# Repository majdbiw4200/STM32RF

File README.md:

# STM32RF
RF to USB design using STM32 microcontroller. The design is a remake of Philip Salmony design https://github.com/pms67/STRF-Kicad

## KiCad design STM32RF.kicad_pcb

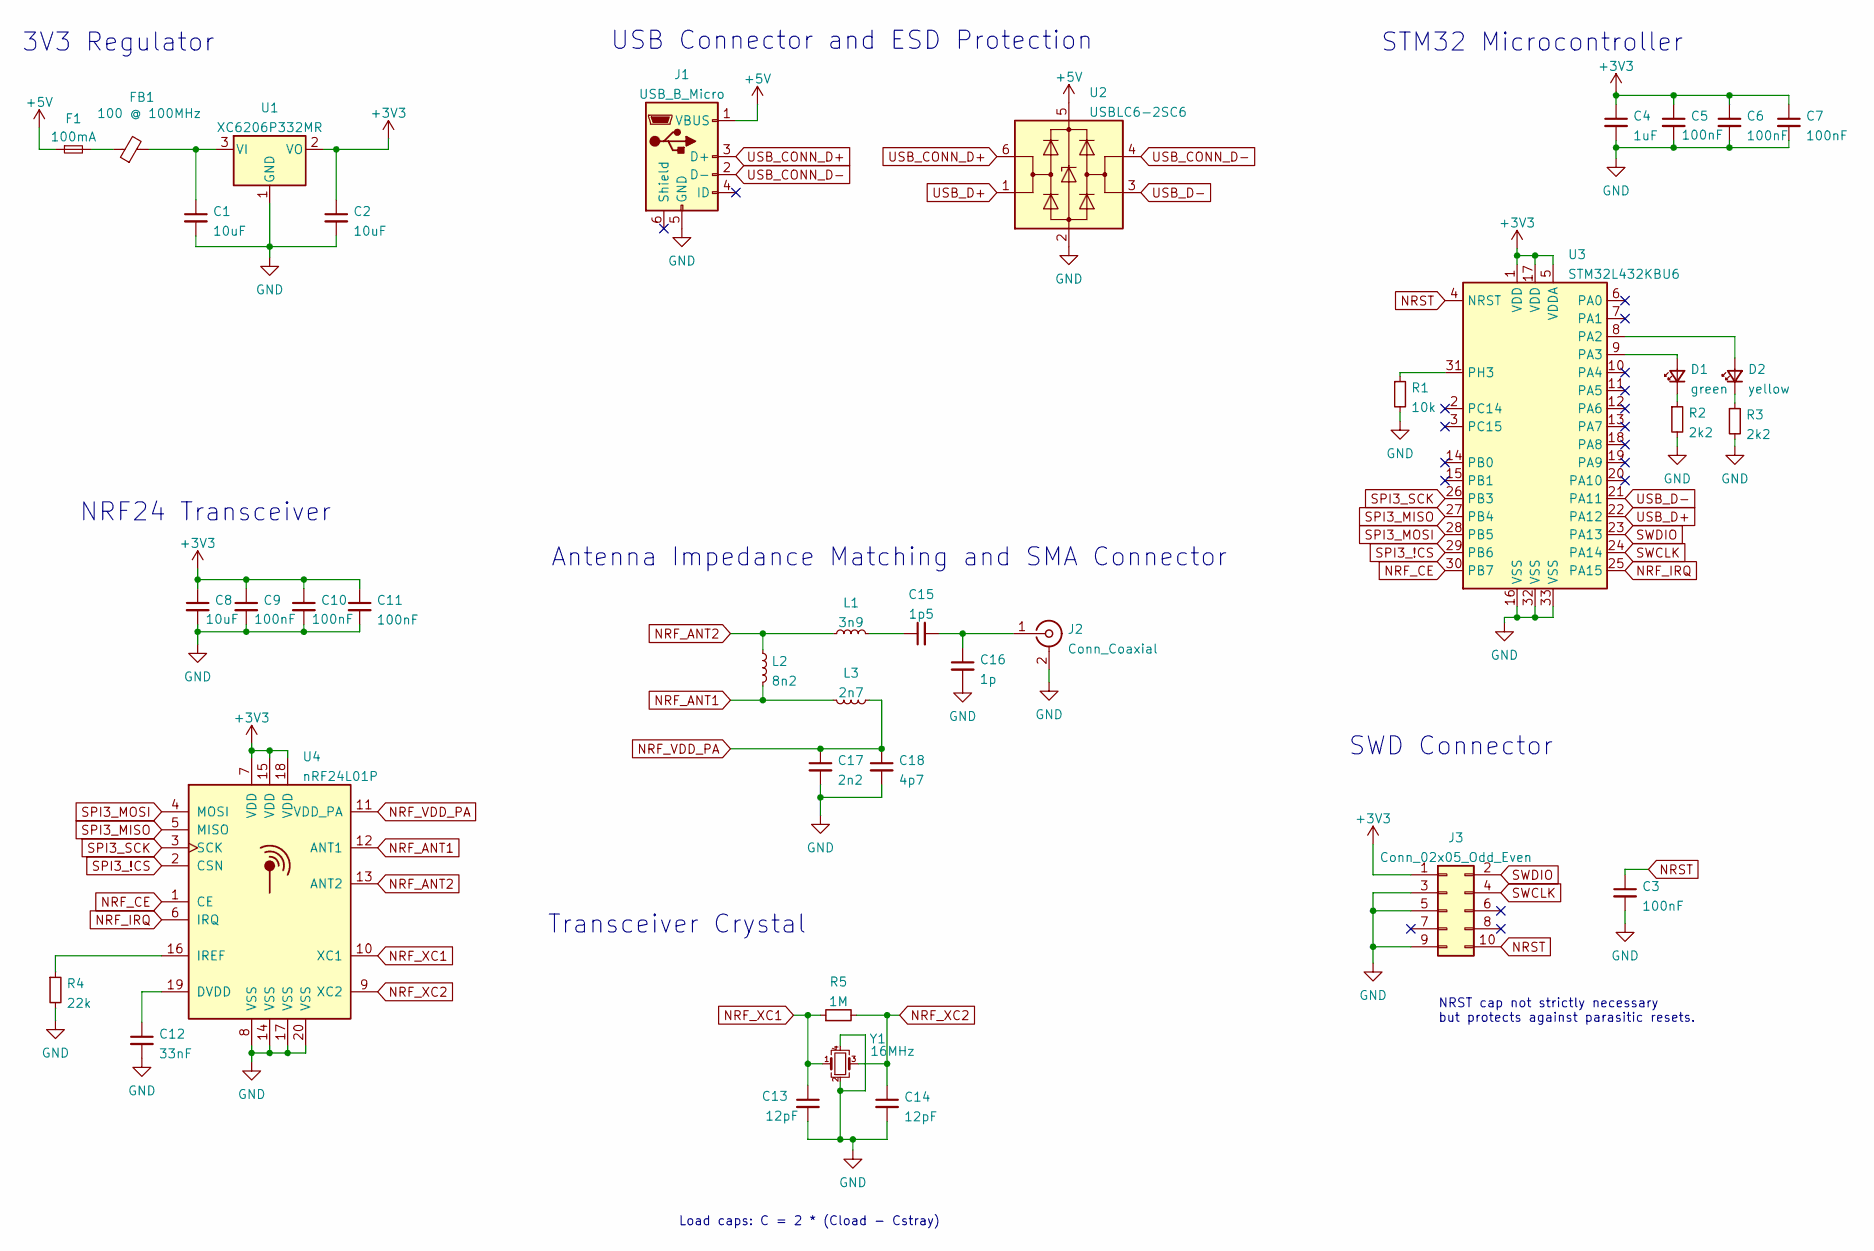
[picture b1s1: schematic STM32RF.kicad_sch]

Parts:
C1, C2, C8: 10uF; C_0603_1608Metric; LCSC Part # C19702
C3, C5, C6, C7, C9, C10, C11: 100nF; C_0402_1005Metric; LCSC Part # C1525
C4: 1uF; C_0402_1005Metric; LCSC Part # C14445
C12: 33nF; C_0402_1005Metric; LCSC Part # C472437
C13, C14: 12pF; C_0402_1005Metric; LCSC Part # C472446
C15: 1p5; C_0402_1005Metric; LCSC Part # C170150
C16: 1p; C_0402_1005Metric; LCSC Part # C307340
C17: 2n2; C_0402_1005Metric; LCSC Part # C84703
C18: 4p7; C_0402_1005Metric; LCSC Part # C318595
D1: green; LED_0603_1608Metric; LCSC Part # C72043
D2: yellow; LED_0603_1608Metric; LCSC Part # C72038
F1: 100mA; Fuse_1206_3216Metric
FB1: 100 @ 100MHz; L_0805_2012Metric; LCSC Part # C1015
J1: USB_B_Micro; USB_Micro-B_Molex_47346-0001
J2: Conn_Coaxial; SMA_Samtec_SMA-J-P-X-ST-EM1_EdgeMount
J3: Conn_02x05_Odd_Even; PinHeader_2x05_P1.27mm_Vertical
L1: 3n9; L_0402_1005Metric; LCSC Part # C14033
L2: 8n2; L_0402_1005Metric; LCSC Part # C16208
L3: 2n7; L_0402_1005Metric; LCSC Part # C27123
R1: 10k; R_0402_1005Metric; LCSC Part # C25744
R2, R3: 2k2; R_0603_1608Metric; LCSC Part # C4190
R4: 22k; R_0402_1005Metric; LCSC Part # C25768
R5: 1M; R_0402_1005Metric; LCSC Part # C26083
U1: XC6206P332MR; SOT-23; LCSC Part # C5446
U2: USBLC6-2SC6; SOT-23-6; LCSC Part # C7519
U3: STM32L432KBU6; QFN-32-1EP_5x5mm_P0.5mm_EP3.45x3.45mm; LCSC Part # C94784
U4: nRF24L01P; QFN-20-1EP_4x4mm_P0.5mm_EP2.5x2.5mm; LCSC Part # C8791
Y1: 16MHz; Crystal_SMD_3225-4Pin_3.2x2.5mm; LCSC Part # C13738

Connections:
+3V3: C2.1, C4.1, C5.1, C6.1, C7.1, C8.1, C9.1, C10.1, C11.1, J3.1, U1.2 (VO), U3.1 (VDD), U3.5 (VDDA), U3.17 (VDD), U4.7 (VDD), U4.15 (VDD), U4.18 (VDD)
+5V: F1.1, J1.1 (VBUS), U2.5 (VBUS)
GND: C1.2, C2.2, C3.2, C4.2, C5.2, C6.2, C7.2, C8.2, C9.2, C10.2, C11.2, C12.2, C13.2, C14.2, C16.2, C17.2, C18.2, J1.5 (GND), J2.2 (Ext), J3.3, J3.5, J3.9, R1.2, R2.2, R3.2, R4.2, U1.1 (GND), U2.2 (GND), U3.16 (VSS), U3.32 (VSS), U3.33 (VSS), U4.8 (VSS), U4.14 (VSS), U4.17 (VSS), U4.20 (VSS), Y1.2, Y1.4
NRF_ANT1: L2.2, L3.2, U4.12 (ANT1)
NRF_ANT2: L1.1, L2.1, U4.13 (ANT2)
NRF_CE: U3.30 (PB7), U4.1 (CE)
NRF_IRQ: U3.25 (PA15), U4.6 (IRQ)
NRF_VDD_PA: C17.1, C18.1, L3.1, U4.11 (VDD_PA)
NRF_XC1: C13.1, R5.1, U4.10 (XC1), Y1.1
NRF_XC2: C14.1, R5.2, U4.9 (XC2), Y1.3
NRST: C3.1, J3.10, U3.4 (NRST)
unnamed: C1.1, FB1.2, U1.3 (VI)
unnamed: C12.1, U4.19 (DVDD)
unnamed: C15.1, L1.2
unnamed: C15.2, C16.1, J2.1 (In)
unnamed: D1.1 (K), R2.1
unnamed: D1.2 (A), U3.9 (PA3)
unnamed: D2.1 (K), R3.1
unnamed: D2.2 (A), U3.8 (PA2)
unnamed: F1.2, FB1.1
unnamed: R1.1, U3.31 (PH3)
unnamed: R4.1, U4.16 (IREF)
SPI3_!CS: U3.29 (PB6), U4.2 (CSN)
SPI3_MISO: U3.27 (PB4), U4.5 (MISO)
SPI3_MOSI: U3.28 (PB5), U4.4 (MOSI)
SPI3_SCK: U3.26 (PB3), U4.3 (SCK)
SWCLK: J3.4, U3.24 (PA14)
SWDIO: J3.2, U3.23 (PA13)
USB_CONN_D+: J1.3 (D+), U2.6 (I/O1)
USB_CONN_D-: J1.2 (D-), U2.4 (I/O2)
USB_D+: U2.1 (I/O1), U3.22 (PA12)
USB_D-: U2.3 (I/O2), U3.21 (PA11)

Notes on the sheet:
NRF24 Transceiver
Transceiver Crystal
SWD Connector
USB Connector and ESD Protection
Load caps: C = 2 * (Cload - Cstray)
NRST cap not strictly necessary but protects against parasitic resets.
Antenna Impedance Matching and SMA Connector
3V3 Regulator
STM32 Microcontroller

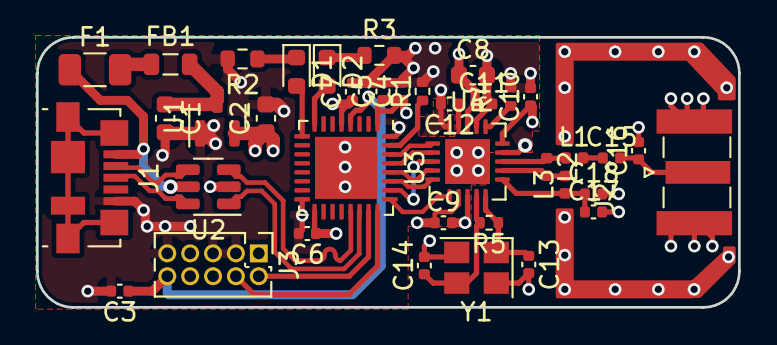
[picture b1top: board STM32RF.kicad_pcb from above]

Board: 4 copper layers, 39.0 x 15.0 mm, 38 parts (0 on the bottom side), 32 nets.

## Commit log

2023-01-10 Add project files
